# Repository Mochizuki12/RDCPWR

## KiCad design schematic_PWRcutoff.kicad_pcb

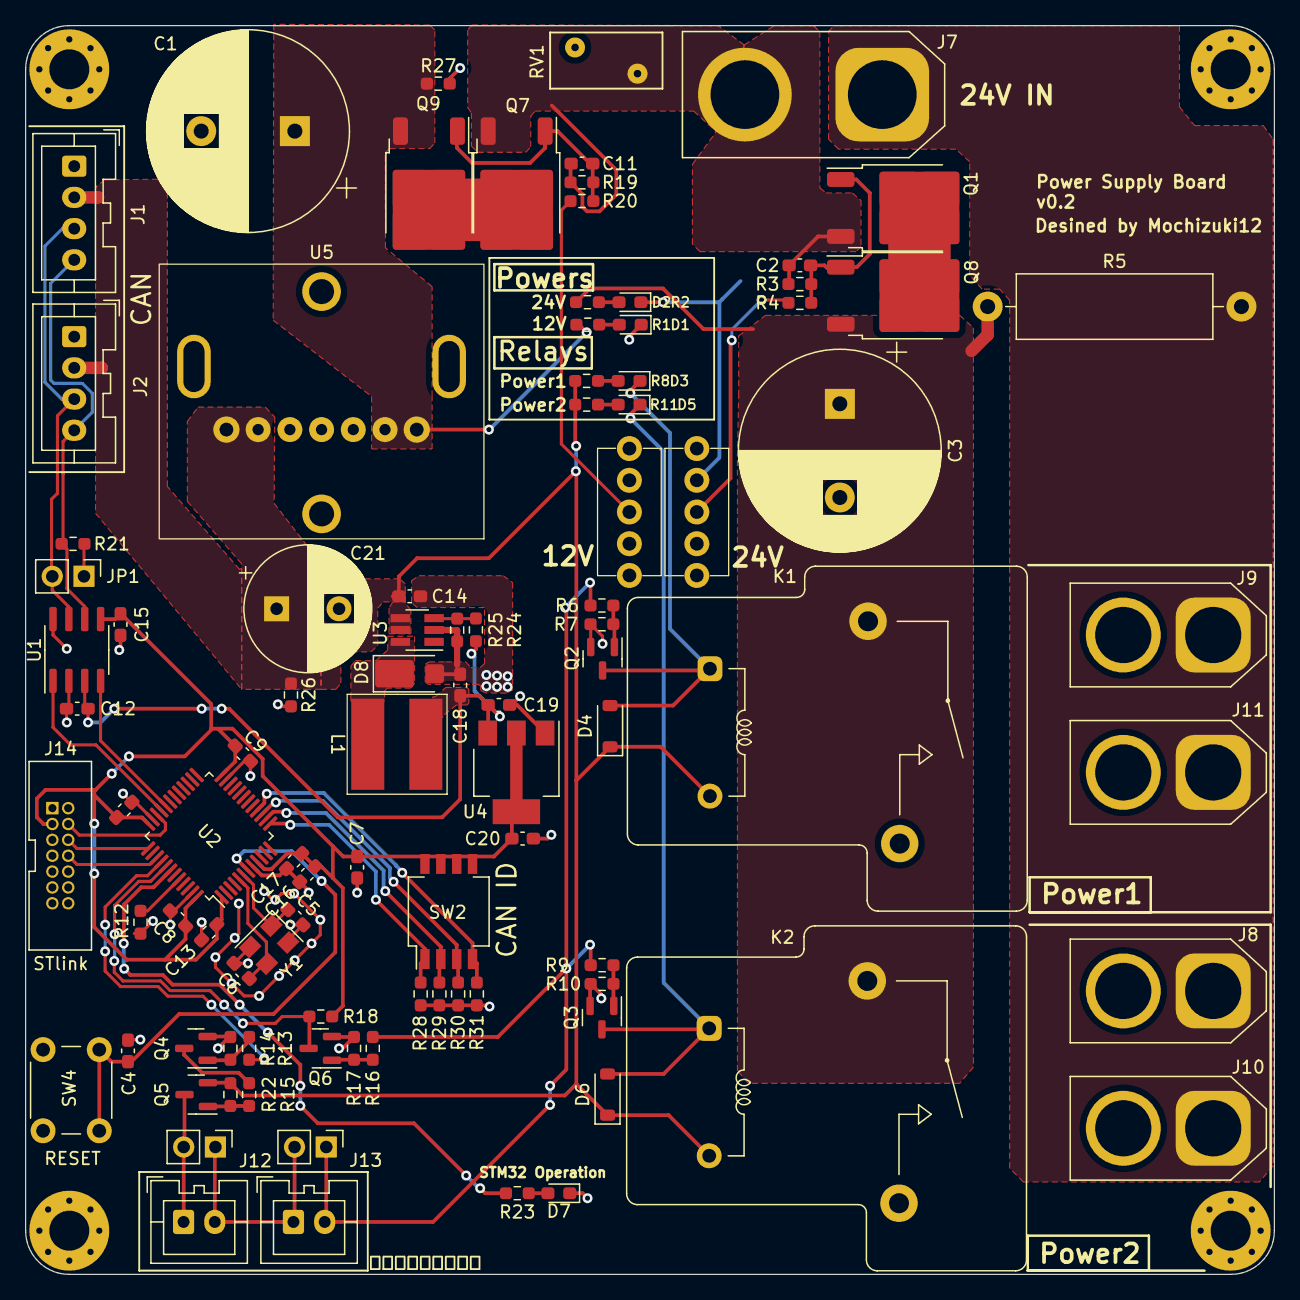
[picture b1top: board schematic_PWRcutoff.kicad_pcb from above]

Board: 2 copper layers, 100.0 x 100.0 mm, 100 parts (0 on the bottom side), 52 nets.

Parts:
C1, C3: 1000uF; CP_Radial_D16.0mm_P7.50mm
C2, C4, C8, C9, C10, C11, C12, C13, C14, C15, C17, C18: 0.1uF; C_0603_1608Metric_Pad1.08x0.95mm_HandSolder
C5, C6: 10pF; C_0603_1608Metric_Pad1.08x0.95mm_HandSolder
C7, C16, C19: 10uF; C_0603_1608Metric_Pad1.08x0.95mm_HandSolder
C20: 22uF; C_0603_1608Metric_Pad1.08x0.95mm_HandSolder
C21: 1000uF; CP_Radial_D10.0mm_P5.00mm
D1, D2, D3, D5, D7: LED; LED_0603_1608Metric_Pad1.05x0.95mm_HandSolder
D4, D6: D; D_SOD-123
D8: MA10EB045; Vishay_SMPA
H1, H2, H3, H4: MountingHole_Pad; MountingHole_3.2mm_M3_Pad_Via
J1, J2: Conn_01x04; JST_XA_B04B-XASK-1_1x04_P2.50mm_Vertical
J7: Conn_01x02; XT90-M
J8, J9, J10, J11: Conn_01x02; AMASS_XT60-F_1x02_P7.20mm_Vertical
J12, J13: Conn_01x02; JST_XA_B02B-XASK-1_1x02_P2.50mm_Vertical
J14: STlink_v3; JTAG_box_connector
JP1, JP2, JP3: Jumper; PinHeader_1x02_P2.54mm_Vertical
K1, K2: RAYEX-L90AS; Relay_SPST_RAYEX-L90AS
L1: 22uH; CDRH6D38
Q1, Q7, Q8, Q9: Q_PMOS_GSD; TO-252-2
Q2, Q3, Q4, Q6: Q_NMOS_GSD; SOT-23
Q5: Q_PMOS_GSD; SOT-23
R1, R2, R3, R4, R7, R8, R10, R11, R12, R14, R15, R17, R18, R19, R20, R22, R23, R24, R25, R26, R27, R28, R29, R30, R31: 10k; R_0603_1608Metric_Pad0.98x0.95mm_HandSolder
R5: 10k; R_Axial_DIN0516_L15.5mm_D5.0mm_P20.32mm_Horizontal
R6, R9, R13, R16: 100; R_0603_1608Metric_Pad0.98x0.95mm_HandSolder
R21: 120; R_0603_1608Metric_Pad0.98x0.95mm_HandSolder
RV1: Varistor; RV_Disc_D9mm_W4.5mm_P5mm
SW1, SW3: SW_SPST; Toggle_switch
SW2: SW_DIP_x04; SW_DIP_SPSTx04_Slide_Copal_CHS-04B_W7.62mm_P1.27mm
SW4: SW_SPST; SW_PUSH_6mm_H7.3mm
U1: MCP2562-H-SN; SOIC-8_3.9x4.9mm_P1.27mm
U2: STM32F103CBTx; LQFP-48_7x7mm_P0.5mm
U3: SOT-23-6_Handsoldering
U4: AZ1117-3.3; SOT-223-3_TabPin2
U5: MPD7K020S
Y1: 12MHz; Crystal_SMD_SeikoEpson_FA238V-4Pin_3.2x2.5mm

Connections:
+3.3V: C7.1, C8.1, C9.1, C10.1, C13.1, C15.2, C16.1, C17.1, C20.1, J14.3, R18.1, SW2.5, SW2.6, SW2.7, SW2.8, U1.5 (Vio), U2.1 (VBAT), U2.9 (VDDA), U2.24 (VDD), U2.36 (VDD), U2.48 (VDD), U4.2 (VO)
+5V: C12.2, C18.1, C19.1, L1.2, R24.1, U1.3 (VDD), U4.3 (VI)
+12V: C14.1, C21.1, D4.1 (K), D6.1 (K), J1.2, J2.2, K1.A2, K2.A2, Q5.2 (S), R8.1, R11.1, R22.1, R26.1, U3.4 (SHDN), U3.5 (VIN), U5.6 (Vout), U5.7 (Vout)
+24V: C2.1, C11.1, J7.2, Q1.3 (S), Q7.3 (S), R3.1, R19.1, RV1.1
/EMS/MCU_EMC_signal: R13.2, U2.40 (PB4)
/EMS/MCU_EMS_Observe: Q6.3 (D), R18.2, U2.41 (PB5)
/EMS/Relay_Signal_OUT: J13.2, JP3.1 (A), R6.2, R9.2, R16.2
/PWR_Cutoff_Relay Sheet1/Relay_SW_OUT: J8.2, J10.2, K2.14
/PWR_Cutoff_Relay Sheet/Relay_SW_OUT: J9.2, J11.2, K1.14
/STM32F103/CAN_ID1: R28.1, SW2.1, U2.13 (PA3)
/STM32F103/CAN_ID2: R29.1, SW2.2, U2.14 (PA4)
/STM32F103/CAN_ID3: R30.1, SW2.3, U2.15 (PA5)
/STM32F103/CAN_ID4: R31.1, SW2.4, U2.16 (PA6)
/STM32F103/CAN_RX: U1.4 (RXD), U2.32 (PA11)
/STM32F103/CAN_TX: U1.1 (TXD), U2.33 (PA12)
/STM32F103/SWCLK: J14.6, U2.37 (PA14)
/STM32F103/SWDIO: J14.4, U2.34 (PA13)
/STM32F103/SWO: J14.8, U2.39 (PB3)
Actuator_Power: C3.1, K1.13, K2.13, Q8.3 (S), R2.1, R5.1
GND: C1.2, C3.2, C4.2, C5.2, C6.2, C7.2, C8.2, C9.2, C10.2, C12.1, C13.2, C14.2, C15.1, C16.2, C17.2, C18.2, C19.2, C20.2, C21.2, D1.1 (K), D2.1 (K), D7.1 (K), D8.2 (A), H1.1, H2.1, H3.1, H4.1, J1.1, J2.1, J7.1, J8.1, J9.1, J10.1, J11.1, J14.5, J14.7, Q2.2 (S), Q3.2 (S), Q4.2 (S), Q6.2 (S), R5.2, R7.2, R10.2, R12.2, R14.2, R17.2, R25.2, R26.2, R27.2, R28.2, R29.2, R30.2, R31.2, RV1.2, SW1.1 (A), SW3.1 (A), SW4.1 (A), U1.2 (VSS), U1.8 (STBY), U2.8 (VSSA), U2.23 (VSS), U2.35 (VSS), U2.47 (VSS), U3.2 (GND), U4.1 (GND), U5.3 (GND), U5.4 (GND), U5.5 (VAR), U5.GND (SHGND), Y1.2, Y1.4
Logic_line_Power: C1.1, Q9.3 (S), R1.1, R27.1, U5.1 (Vin), U5.2 (Vin)
MCU_running: R23.1, U2.42 (PB6)
unnamed: D1.2 (A), R1.2
unnamed: D2.2 (A), R2.2
unnamed: D3.2 (A), R8.2
unnamed: D3.1 (K), D4.2 (A), K1.A1, Q2.3 (D)
unnamed: D5.2 (A), R11.2
unnamed: D5.1 (K), D6.2 (A), K2.A1, Q3.3 (D)
unnamed: D7.2 (A), R23.2
unnamed: D8.1 (K), L1.1, U3.6 (SW)
unnamed: J1.3, J2.3, JP1.2 (B), U1.7 (CANH)
unnamed: J1.4, J2.4, R21.2, U1.6 (CANL)
unnamed: J12.1, JP2.2 (B), Q5.3 (D)
unnamed: J12.2, J13.1, JP2.1 (A), JP3.2 (B)
unnamed: JP1.1 (A), R21.1
unnamed: Q1.2 (D), Q8.2 (D)
unnamed: C2.2, Q1.1 (G), Q8.1 (G), R3.2, R4.1
unnamed: Q2.1 (G), R6.1, R7.1
unnamed: Q3.1 (G), R9.1, R10.1
unnamed: Q4.3 (D), R15.2
unnamed: Q4.1 (G), R13.1, R14.1
unnamed: Q5.1 (G), R15.1, R22.2
unnamed: Q6.1 (G), R16.1, R17.1
unnamed: Q7.2 (D), Q9.2 (D)
unnamed: C11.2, Q7.1 (G), Q9.1 (G), R19.2, R20.1
unnamed: R4.2, SW1.2 (B)
unnamed: R20.2, SW3.2 (B)
unnamed: C4.1, SW4.2 (B), U2.7 (NRST)
unnamed: R12.1, U2.44 (BOOT0)
unnamed: C6.1, U2.5 (PD0), Y1.3
unnamed: C5.1, U2.6 (PD1), Y1.1
unnamed: R24.2, R25.1, U3.3 (FB)

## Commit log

2024-11-13 add STM32F103
2024-11-13 add switch, EMS & MCU
2024-11-16 precompreate design
